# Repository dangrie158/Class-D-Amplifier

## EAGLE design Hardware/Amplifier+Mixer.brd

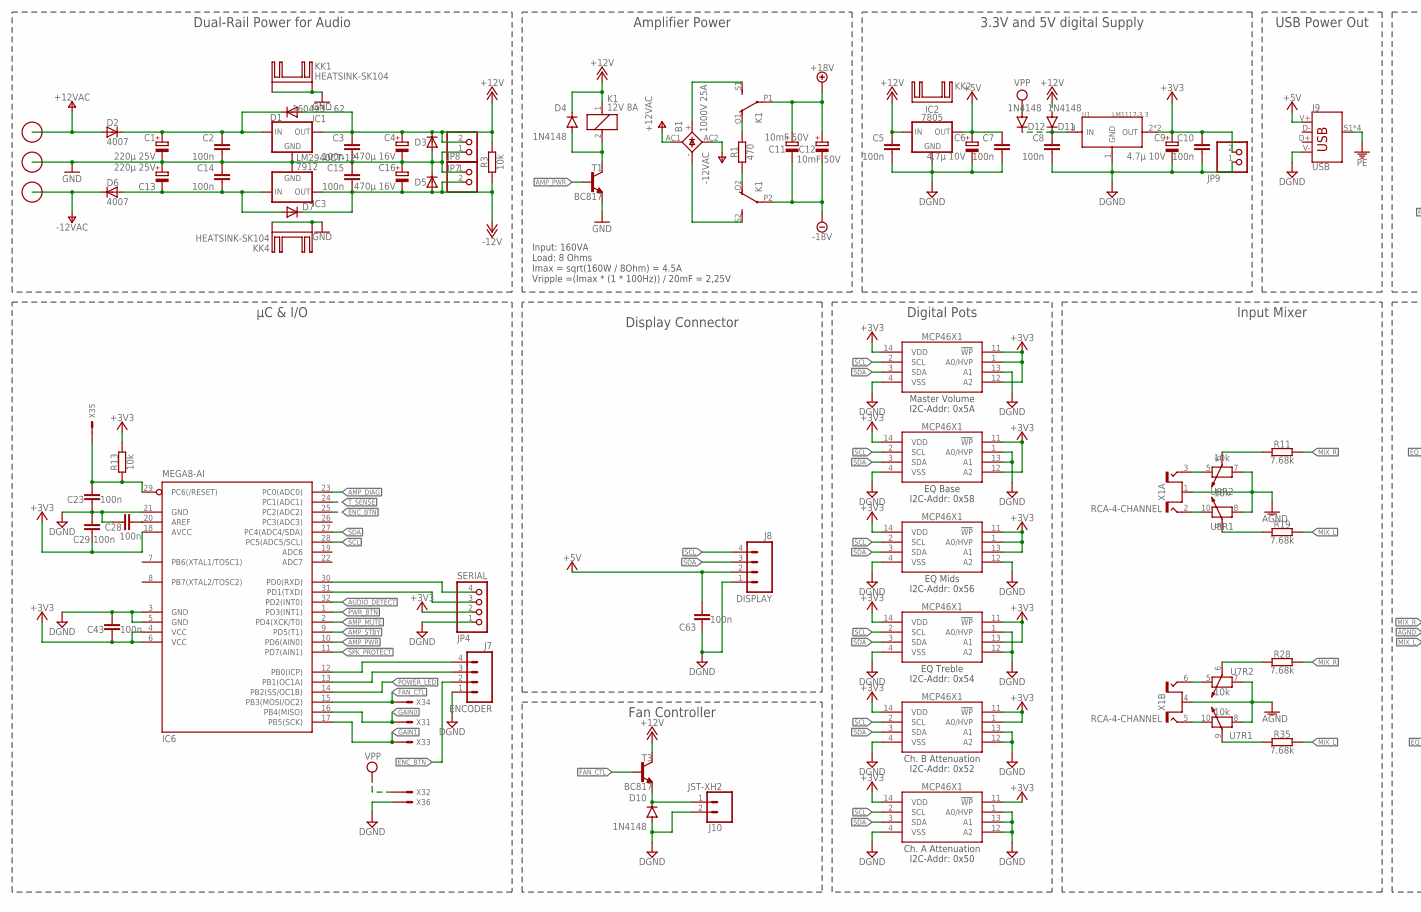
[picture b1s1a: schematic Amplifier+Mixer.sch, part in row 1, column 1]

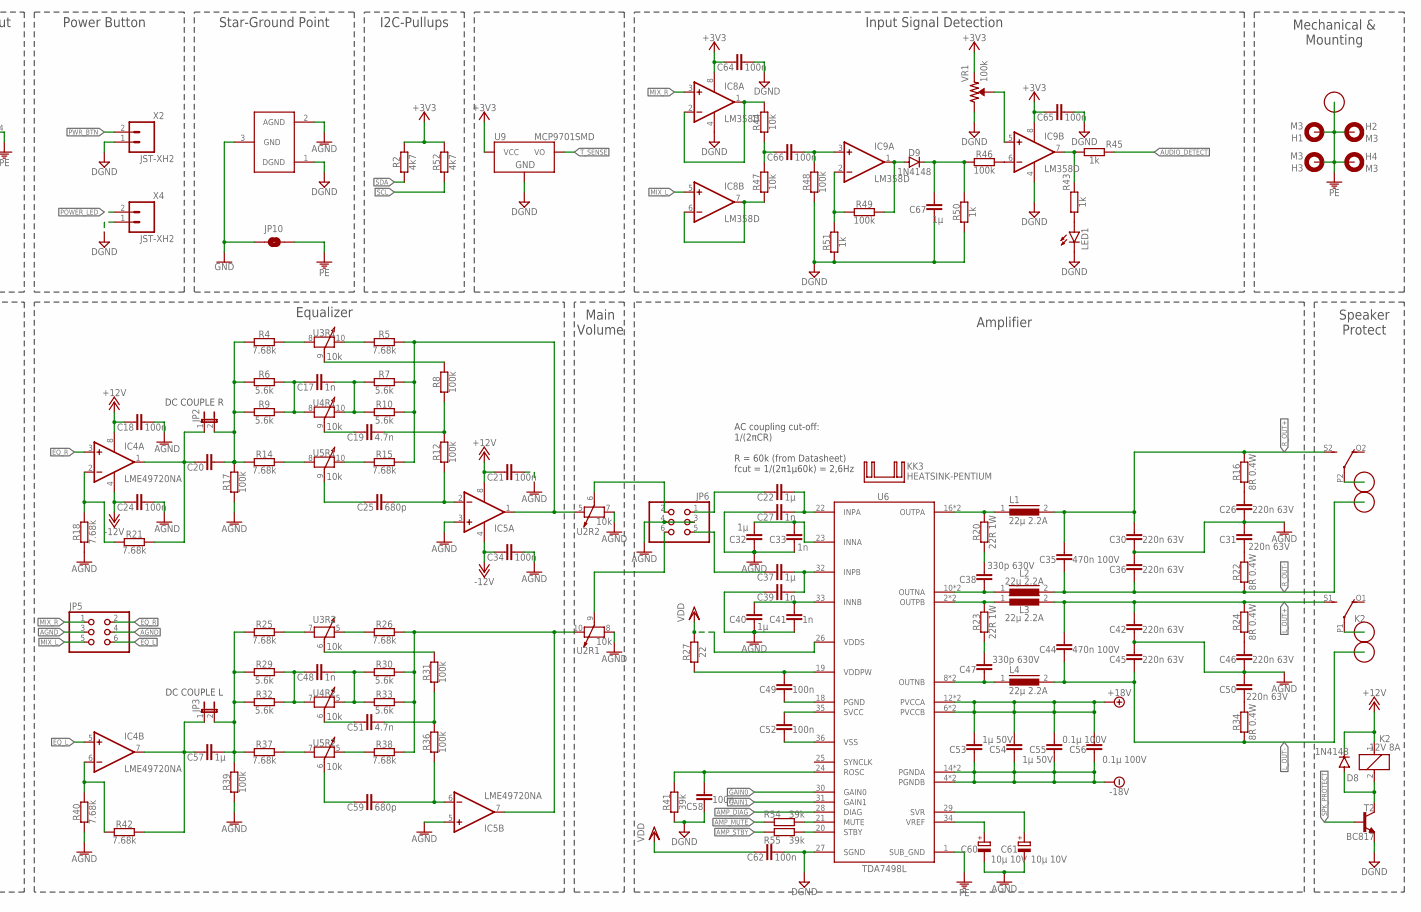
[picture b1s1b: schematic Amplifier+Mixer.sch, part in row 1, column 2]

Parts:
B1: 1000V 25A; FB100; MOUSER 833-GBJL2510-BP
C1, C13: 220µ 25V; 175TMP-0810; MOUSER 647-UWT1E221MNL1GS
C2, C3, C5, C7, C8, C10, C14, C15, C18, C21, C23, C24, C28, C29, C34, C43, C49, C52, C58, C62, C63, C64, C65, C66: 100n; C0603; MOUSER 710-885012206071
C4, C16: 470µ 16V; 175TMP-0810; MOUSER 647-UWT1C471MNL1S
C6, C9: 4.7µ 10V; 153CLV-0505; MOUSER 710-865230642008
C11, C12: 10mF 50V; EB35D; MOUSER 647-LLS1H103MELC
C17, C27, C33, C39, C41, C48: 1n; C050-025X075; MOUSER 80-R82EC1100AA50K
C19, C51: 4.7n; C075-032X103; MOUSER 594-222237188472
C20: DC COUPLE L; C050-050X075; MOUSER 80-R82DC4100AA60K
C22, C32, C37, C40, C57: 1µ; C050-050X075; MOUSER 80-R82DC4100AA60K
C25, C59: 680p; C050-045X075; MOUSER 505-FKP2J006801D00KS
C26, C30, C31, C36, C42, C45, C46, C50: 220n 63V; C050-025X075; MOUSER 80-R82DC3220AA60K
C35, C44: 470n 100V; C050-045X075; MOUSER 505-MKS2D034701E00JI
C38, C47: 330p 630V; C050-045X075; MOUSER 505-FKP2C003301D00KI
C53, C54: 1µ 50V; C1206K; MOUSER 80-C1206C105M5RECLR
C55, C56: 0.1µ 100V; C1206K; MOUSER 77-VJ1206Y104KXBAT
C60, C61: 10µ 10V; 153CLV-0505; MOUSER 710-865080642006
C67: 1µ; C0603; MOUSER 710-885012106022
D1, D2, D3, D5, D6, D7: 4007; SODFL5024X231; MOUSER 583-FM4007W-W
D4, D8, D9, D10, D11, D12: 1N4148; SOD-323; MOUSER 512-1N4148WS
H1, H2, H3, H4: M3; 3,0-PAD
IC1: LM2940CT-12; 78XXS; MOUSER 511-L7812CV
IC2: 7805; 78XXS; MOUSER 511-L7805CV
IC3: 7912; 79XXS; MOUSER 511-L7912CV
IC4, IC5: LME49720NA; DIL08
IC6: MEGA8-AI; TQFP32-08; MOUSER 556-ATMEGA328-AU
IC8, IC9: LM358D; SO08; MOUSER 511-LM358DT
J1, J2, J3, J4: 6MM; TE-726386; MOUSER 571-726386-2
J5, J6: TERMINAL-BLOCK-2PLUG-IN; MSTBV2; MOUSER 651-1954919
J7: ENCODER; JST-4-PTH-VERT; MOUSER 538-35312-0260
J8: DISPLAY; JST-4-PTH-VERT; MOUSER 538-35312-0260
J9: USB; ECON-USBBUVA; MOUSER 523-GSB19110KEU
J10: JST-XH2; JST-2-PTH-VERT; MOUSER 575-3191010200006000
JP1: GND_CONNECT
JP2: DC COULE R; JP1; MOUSER 200-TSW10223TS
JP3: DC COUPLE L; JP1; MOUSER 200-TSW10223TS
JP4: SERIAL; 1X04; MOUSER 649-68001-204HLF
JP5: MIX OUT; 2X03
JP6: PREAMP OUT; 2X03
JP7, JP8, JP9: PINHD-1X2; 1X02
JP10: PEGND; SMT-JUMPER_2_NO_NO-SILK
K1, K2: 12V 8A; F4052; MOUSER 655-RT424012
KK1, KK4: HEATSINK-SK104; SK104-PAD; MOUSER 490-HSE-B20254-035H
KK2: HEATSINK-SK95; SK95-2M3; MOUSER 490-HSE-B2111-038
KK3: HEATSINK-PENTIUM
L1, L2, L3, L4: 22µ 2.2A; INDUCTOR-12MM; MOUSER 710-744771220
LED1: LEDCHIP-LED0603; CHIP-LED0603
R1: 470; 0617/22; MOUSER 279-EP5WS470RJ
R2, R52: 4k7; R0603; MOUSER 603-AC0603JR-134K7L
R3, R13, R44, R47: 10k; R0603; MOUSER 603-RC0603FR-0710KL
R4, R5, R11, R14, R15, R18, R19, R21, R25, R26, R28, R35, R37, R38, R40, R42: 7.68k; MINI_MELF-0207W; MOUSER 71-SMM02070C7501FBP0
R6, R7, R9, R10, R29, R30, R32, R33: 5.6k; MINI_MELF-0207W; MOUSER 71-SMM02070C5601FBP0
R8, R12, R17, R31, R36, R39: 100k; MINI_MELF-0204W; MOUSER 756-WRM024HPC100KFT3
R16, R22, R24, R34: 8R 0.4W; MINI_MELF-0204W; MOUSER 756-WRM0204HPC8R2FT3
R20, R23: 22R 1W; MINI_MELF-0207W; MOUSER 756-WRM0207HPC22RFT2
R27: 22; R0603; MOUSER 603-RC0603FR-0722RL
R41: 39k; R0603; MOUSER 603-RC0603FR-0739KL
R43, R45, R50, R51: 1k; R0603; MOUSER 603-RC0603FR-071KL
R46, R48, R49: 100k; R0603; MOUSER 71-RCA0603100KJNEC
R54, R55: 39k; R0603; MOUSER 71-RCA0603100KJNEC
T1, T2, T3: BC817; SOT23-BEC; MOUSER 863-BC817-16LT3G
U1: LM1117-3.3; SOT-223; MOUSER 926-LM1117MPX3.3NOPB
U2, U3, U4, U5, U7, U8: 10k; SOP65P640X120-14; MOUSER 579-MCP4641-103E/ST
U6: TDA7498L; SOP50P1010X245-36; MOUSER 511-TDA7498TR
U9: MCP9701SMD; SOT23-3
VR1: 100k; TRIMPOT-SMD-TC33X; MOUSER 858-35WR100KLFTR
X1: RCA-4-CHANNEL; BKL-072385; MOUSER 806-KLP42X-61-WWRR
X2, X4: JST-XH2; JST-2-PTH-VERT; MOUSER 575-3191010200006000
X3: ICSP; 057-006-1; MOUSER 200-TSW10307TD

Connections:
+3V3: C9.+, C10.1, C29.1, C43.1, C64.1, C65.1, IC6.4 (VCC), IC6.6 (VCC), IC6.18 (AVCC), IC8.8 (V+), IC9.8 (V+), JP4.2, JP9.2, R2.2, R13.2, R52.2, U1.2 (OUT), U1.TER (OUT), U2.1 (A0/HVP), U2.11 (!WP), U2.12 (A2), U2.14 (VDD), U3.11 (!WP), U3.12 (A2), U3.14 (VDD), U4.1 (A0/HVP), U4.11 (!WP), U4.13 (A1), U4.14 (VDD), U5.11 (!WP), U5.13 (A1), U5.14 (VDD), U7.1 (A0/HVP), U7.11 (!WP), U7.14 (VDD), U8.11 (!WP), U8.14 (VDD), U9.1 (VCC), VR1.3 (CCW)
+5V: C6.+, C7.1, C63.2, IC2.OUT, J8.2, J9.V+ (VBUS)
+12V: C3.1, C4.+, C5.1, C18.1, C21.1, D1.A, D3.C, D4.C, D8.C, D11.A, IC1.OUT, IC2.IN, IC4.8 (V+), IC5.8 (V+), JP7.2, K1.1, K2.1, R3.1, T3.C
+18V: C11.+, C12.+, C53.1, C54.1, C55.1, C56.1, K1.P1, U6.6 (PVCCB), U6.7 (PVCCB), U6.12 (PVCCA), U6.13 (PVCCA)
-12V: C15.2, C16.-, C24.1, C34.1, D5.A, D7.C, IC3.OUT, IC4.4 (V-), IC5.4 (V-), JP8.2, R3.2
-18V: C11.-, C12.-, C53.2, C54.2, C55.2, C56.2, K1.P2, U6.4 (PGNDB), U6.5 (PGNDB), U6.14 (PGNDA), U6.15 (PGNDA)
AGND: C18.2, C21.2, C24.2, C26.2, C27.1, C30.2, C31.1, C32.1, C33.1, C34.2, C36.1, C39.1, C40.1, C41.1, C42.2, C45.1, C46.2, C50.1, C60.-, C61.-, IC5.3 (+IN), IC5.5 (+IN), JP1.2 (AGND), JP5.3, JP5.4, JP6.3, JP6.4, R17.1, R18.2, R39.1, R40.2, U2.7 (A), U2.8 (A), U7.7 (A), U7.8 (A), U8.7 (A), U8.8 (A), X1.1 (S), X1.4 (S)
AMP_DIAG: IC6.23 (PC0(ADC0)), U6.28 (DIAG)
AMP_MUTE: IC6.2 (PD4(XCK/T0)), R54.2
AMP_MUTE_CL: R54.1, U6.21 (MUTE)
AMP_PWR: IC6.10 (PD6(AIN0)), T1.B
AMP_STBY: IC6.9 (PD5(T1)), R55.2
AMP_STBY_CL: R55.1, U6.20 (STBY)
AUDIO_DETECT: IC6.32 (PD2(INT0)), R45.1
DGND: C5.2, C6.-, C7.2, C8.2, C9.-, C10.2, C23.1, C28.2, C29.2, C43.2, C58.2, C62.1, C63.1, C64.2, C65.2, C67.1, D10.A, IC2.GND, IC6.3 (GND), IC6.5 (GND), IC6.21 (GND), IC8.4 (V-), IC9.4 (V-), J7.1, J8.1, J9.V- (GND), J10.2, JP1.1 (DGND), JP4.1, JP9.1, LED1.C, R41.1, R48.1, R50.1, R51.1, T2.E, U1.1 (GND), U2.4 (VSS), U2.13 (A1), U3.1 (A0/HVP), U3.4 (VSS), U3.13 (A1), U4.4 (VSS), U4.12 (A2), U5.1 (A0/HVP), U5.4 (VSS), U5.12 (A2), U6.27 (SGND), U7.4 (VSS), U7.12 (A2), U7.13 (A1), U8.1 (A0/HVP), U8.4 (VSS), U8.12 (A2), U8.13 (A1), U9.3 (GND), VR1.1 (CW), X2.1, X3.6, X4.1
ENC_BTN: IC6.25 (PC2(ADC2)), J7.2
EQ_L: IC4.5 (+IN), JP5.6
EQ_OUT_L: IC5.7 (OUT), R26.1, R30.1, R33.1, R38.1, U2.10 (B)
EQ_OUT_R: IC5.1 (OUT), R5.1, R7.1, R10.1, R15.1, U2.5 (B)
EQ_R: IC4.3 (+IN), JP5.2
FAN_CTL: IC6.15 (PB3(MOSI/OC2)), T3.B, X3.4
GAIN0: IC6.16 (PB4(MISO)), U6.30 (GAIN0), X3.1
GAIN1: IC6.17 (PB5(SCK)), U6.31 (GAIN1), X3.3
GND: C1.-, C2.2, C3.2, C4.-, C13.+, C14.1, C15.1, C16.+, D3.A, D5.C, IC1.GND, IC3.GND, J2.P$1, J2.P$2, JP1.3 (GND), JP7.1, JP8.1, JP10.1, KK1.K1, KK1.K2, KK4.K1, KK4.K2, T1.E
INNA: C32.2, C33.2, U6.23 (INNA)
INNB: C40.2, C41.2, U6.33 (INNB)
INPA: C22.2, C27.2, U6.22 (INPA)
INPB: C37.2, C39.2, U6.32 (INPB)
L_OUT+: C42.1, C44.1, K2.S1 (S), L3.2, R24.2
L_OUT-: C44.2, C45.2, J6.1, L4.2, R34.1
MIX_AMP_L: C57.1, IC4.7 (OUT), JP3.1, R42.1
MIX_AMP_R: C20.1, IC4.1 (OUT), JP2.1, R21.1
MIX_L: IC8.5 (+IN), JP5.5, R19.2, R35.2
MIX_R: IC8.3 (+IN), JP5.1, R11.2, R28.2
unnamed: C20.2, JP2.2, R4.2, R6.2, R9.2, R14.2, R17.2
unnamed: R14.1, U5.8 (A)
unnamed: C25.2, U5.9 (W)
unnamed: R15.2, U5.10 (B)
unnamed: C17.1, R6.1, R9.1, U4.8 (A)
unnamed: C57.2, JP3.2, R25.2, R29.2, R32.2, R37.2, R39.2
unnamed: R8.2, U3.9 (W)
unnamed: R31.2, U3.6 (W)
unnamed: B1.+, K1.S1 (S)
unnamed: R26.2, U3.5 (B)
unnamed: C19.2, U4.9 (W)
unnamed: C19.1, R8.1, R12.2
unnamed: C66.1, R44.1, R47.2
unnamed: R25.1, U3.7 (A)
unnamed: C17.2, R7.2, R10.2, U4.10 (B)
unnamed: C59.2, U5.6 (W)
unnamed: C51.2, U4.6 (W)
unnamed: R4.1, U3.8 (A)
unnamed: C48.1, R29.1, R32.1, U4.7 (A)
unnamed: C48.2, R30.2, R33.2, U4.5 (B)
unnamed: R37.1, U5.7 (A)
unnamed: R38.2, U5.5 (B)
unnamed: C13.-, C14.2, D6.A, D7.A, IC3.IN
unnamed: C1.+, C2.1, D1.C, D2.C, IC1.IN
unnamed: C66.2, IC9.3 (+IN), R48.2
unnamed: C52.2, U6.36 (VSS)
unnamed: B1.-, K1.S2 (S)
unnamed: R5.2, U3.10 (B)
unnamed: C51.1, R31.1, R36.2
unnamed: C52.1, U6.35 (SVCC)
unnamed: IC9.2 (-IN), R49.2, R51.2
unnamed: D9.A, IC9.1 (OUT), R49.1
unnamed: C67.2, D9.C, R46.2, R50.2
unnamed: IC9.6 (-IN), R46.1
unnamed: IC9.5 (+IN), VR1.2 (WIPER)
unnamed: IC9.7 (OUT), R43.1, R45.2
unnamed: LED1.A, R43.2
unnamed: IC8.6 (-IN), IC8.7 (OUT), R47.1
unnamed: IC8.1 (OUT), IC8.2 (-IN), R44.2
unnamed: U7.5 (B), X1.6 (T2)
unnamed: U7.10 (B), X1.5 (T1)
unnamed: R35.1, U7.9 (W)
unnamed: R28.1, U7.6 (W)
unnamed: IC4.6 (-IN), R40.1, R42.2
unnamed: IC4.2 (-IN), R18.1, R21.2
unnamed: U8.5 (B), X1.3 (T2)
unnamed: U8.10 (B), X1.2 (T1)
unnamed: R19.1, U8.9 (W)
unnamed: R11.1, U8.6 (W)
unnamed: D4.A, K1.2, T1.C
unnamed: J6.2, K2.P1
unnamed: K1.O1 (O), R1.1
unnamed: C58.1, R41.2, U6.24 (ROSC)
unnamed: C49.1, R27.1, U6.19 (VDDPW)
unnamed: C49.2, U6.18 (PGND)
unnamed: C8.1, D11.C, D12.C, U1.3 (IN)
unnamed: K1.O2 (O), R1.2
unnamed: J5.1, K2.P2
unnamed: C50.2, R34.2
unnamed: D10.C, J10.1, T3.E
unnamed: C46.1, R24.1
unnamed: C60.+, U6.34 (VREF)
unnamed: C61.+, U6.29 (SVR)
unnamed: C31.2, R22.2
unnamed: C26.1, R16.1
unnamed: C47.2, L4.1, U6.8 (OUTNB), U6.9 (OUTNB)
unnamed: C38.2, L2.1, U6.10 (OUTNA), U6.11 (OUTNA)
unnamed: C38.1, R20.1
unnamed: C47.1, R23.1
unnamed: L1.1, R20.2, U6.16 (OUTPA), U6.17 (OUTPA)
unnamed: L3.1, R23.2, U6.2 (OUTPB), U6.3 (OUTPB)
unnamed: D8.A, K2.2, T2.C
unnamed: IC6.13 (PB1(OC1A)), J7.3
unnamed: C28.1, IC6.20 (AREF)
unnamed: IC6.12 (PB0(ICP)), J7.4
unnamed: C22.1, JP6.1
unnamed: C23.2, IC6.29 (PC6(/RESET)), R13.1, X3.5
unnamed: C37.1, JP6.5
unnamed: IC6.30 (PD0(RXD)), JP4.4
unnamed: IC6.31 (PD1(TXD)), JP4.3
OUT_L_DAMPED: C59.1, IC5.6 (-IN), R36.1
OUT_R_DAMPED: C25.1, IC5.2 (-IN), R12.1
PE: H1.B3,0, H2.B3,0, H3.B3,0, H4.B3,0, J4.P$1, J4.P$2, J9.S1 (SHIELD), J9.S2 (SHIELD), J9.S3 (SHIELD), J9.S4 (SHIELD), JP10.2, U6.1 (SUB_GND)
POWER_LED: IC6.14 (PB2(SS/OC1B)), X4.2
PREAMP_OUT_L: JP6.6, U2.9 (W)
PREAMP_OUT_R: JP6.2, U2.6 (W)
PWR_BTN: IC6.1 (PD3(INT1)), X2.2
R_OUT+: C30.1, C35.1, K2.S2 (S), L1.2, R16.2
R_OUT-: C35.2, C36.2, J5.2, L2.2, R22.1
SCL: IC6.28 (PC5(ADC5/SCL)), J8.4, R52.1, U2.2 (SCL), U3.2 (SCL), U4.2 (SCL), U5.2 (SCL), U7.2 (SCL), U8.2 (SCL)
SDA: IC6.27 (PC4(ADC4/SDA)), J8.3, R2.1, U2.3 (SDA), U3.3 (SDA), U4.3 (SDA), U5.3 (SDA), U7.3 (SDA), U8.3 (SDA)
SPK_PROTECT: IC6.11 (PD7(AIN1)), T2.B
T_SENSE: IC6.24 (PC1(ADC1)), U9.2 (VO)
V+: B1.AC1, D2.A, J1.P$1, J1.P$2
V-: B1.AC2, D6.C, J3.P$1, J3.P$2
VDD: C62.2, R27.2, U6.26 (VDDS)
VPP: D12.A, X3.2

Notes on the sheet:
I2C-Addr: 0x50
I2C-Addr: 0x52
I2C-Addr: 0x54
I2C-Addr: 0x56
I2C-Addr: 0x58
I2C-Addr: 0x5A
Ch. A Attenuation
Ch. B Attenuation
EQ Treble
EQ Mids
EQ Base
Master Volume
Amplifier
Speaker Protect
Main Volume
Equalizer
Input Mixer
Digital Pots
Display Connector
Fan Controller
µC & I/O
Input Signal Detection
Amplifier Power
Dual-Rail Power for Audio
3.3V and 5V digital Supply
USB Power Out
Power Button
Star-Ground Point
Mechanical & Mounting
I2C-Pullups
DC COUPLE L
DC COUPLE R
Input: 160VA Load: 8 Ohms Imax = sqrt(160W / 8Ohm) = 4.5A Vripple =(Imax * (1 * 100Hz)) / 20mF = 2,25V
AC coupling cut-off: 1/(2πCR) R = 60k (from Datasheet) fcut = 1/(2π1µ60k) = 2,6Hz

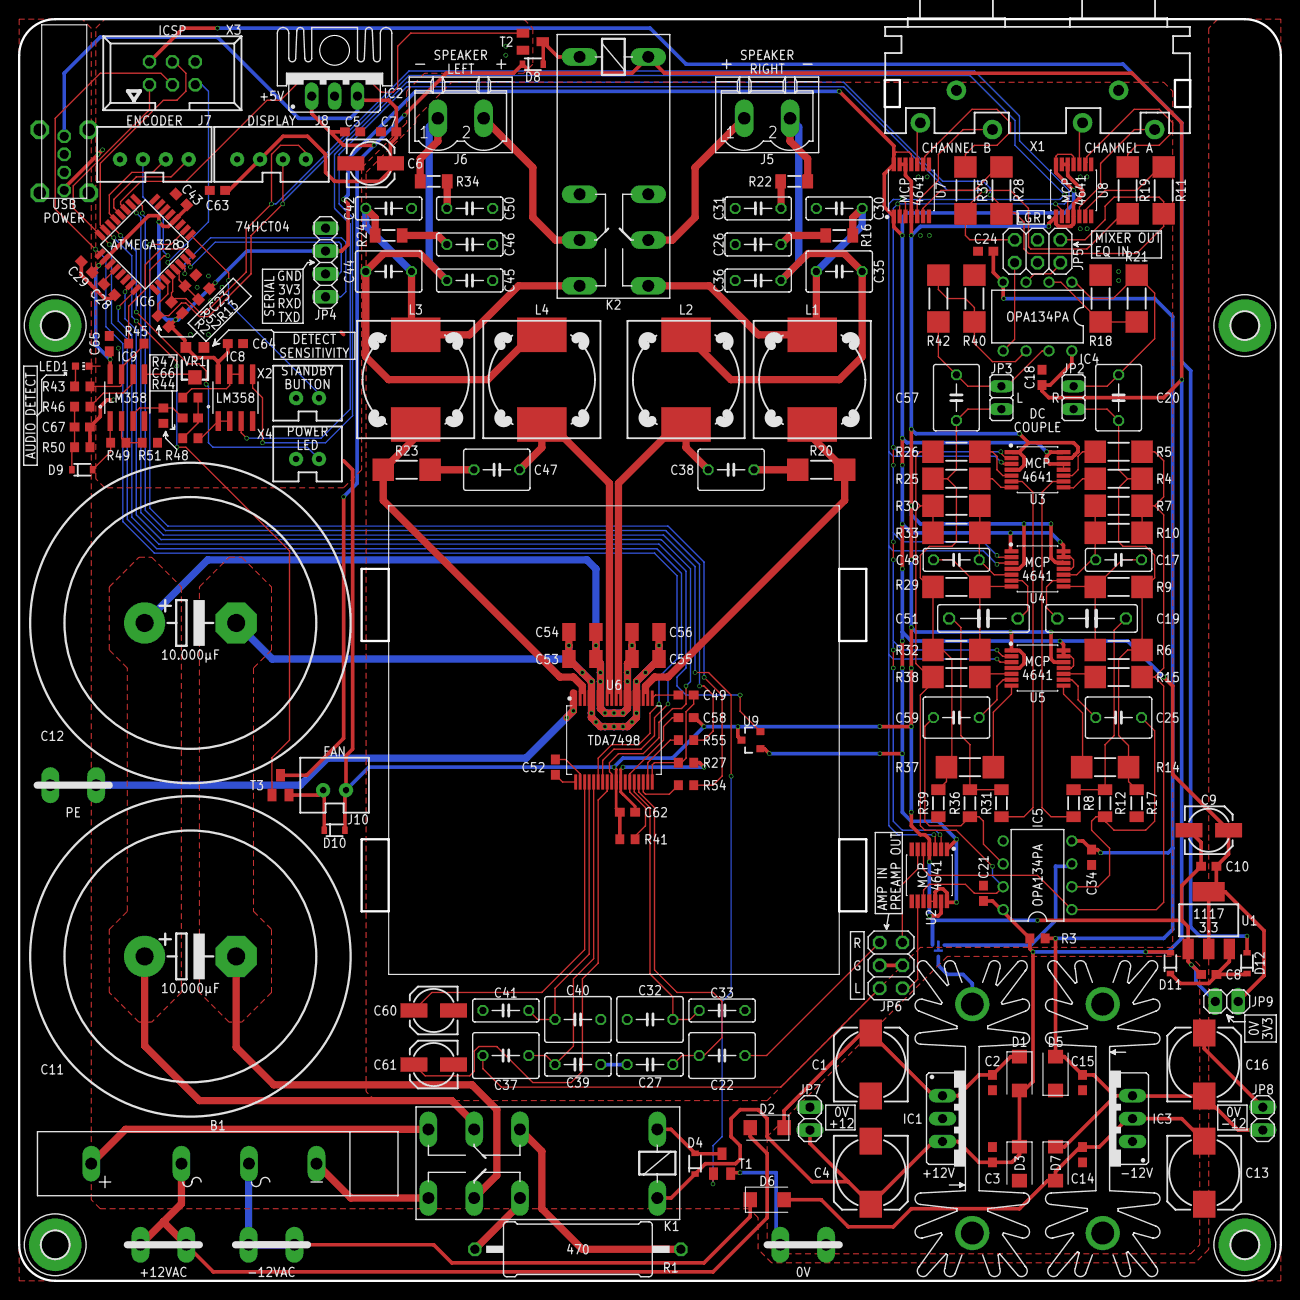
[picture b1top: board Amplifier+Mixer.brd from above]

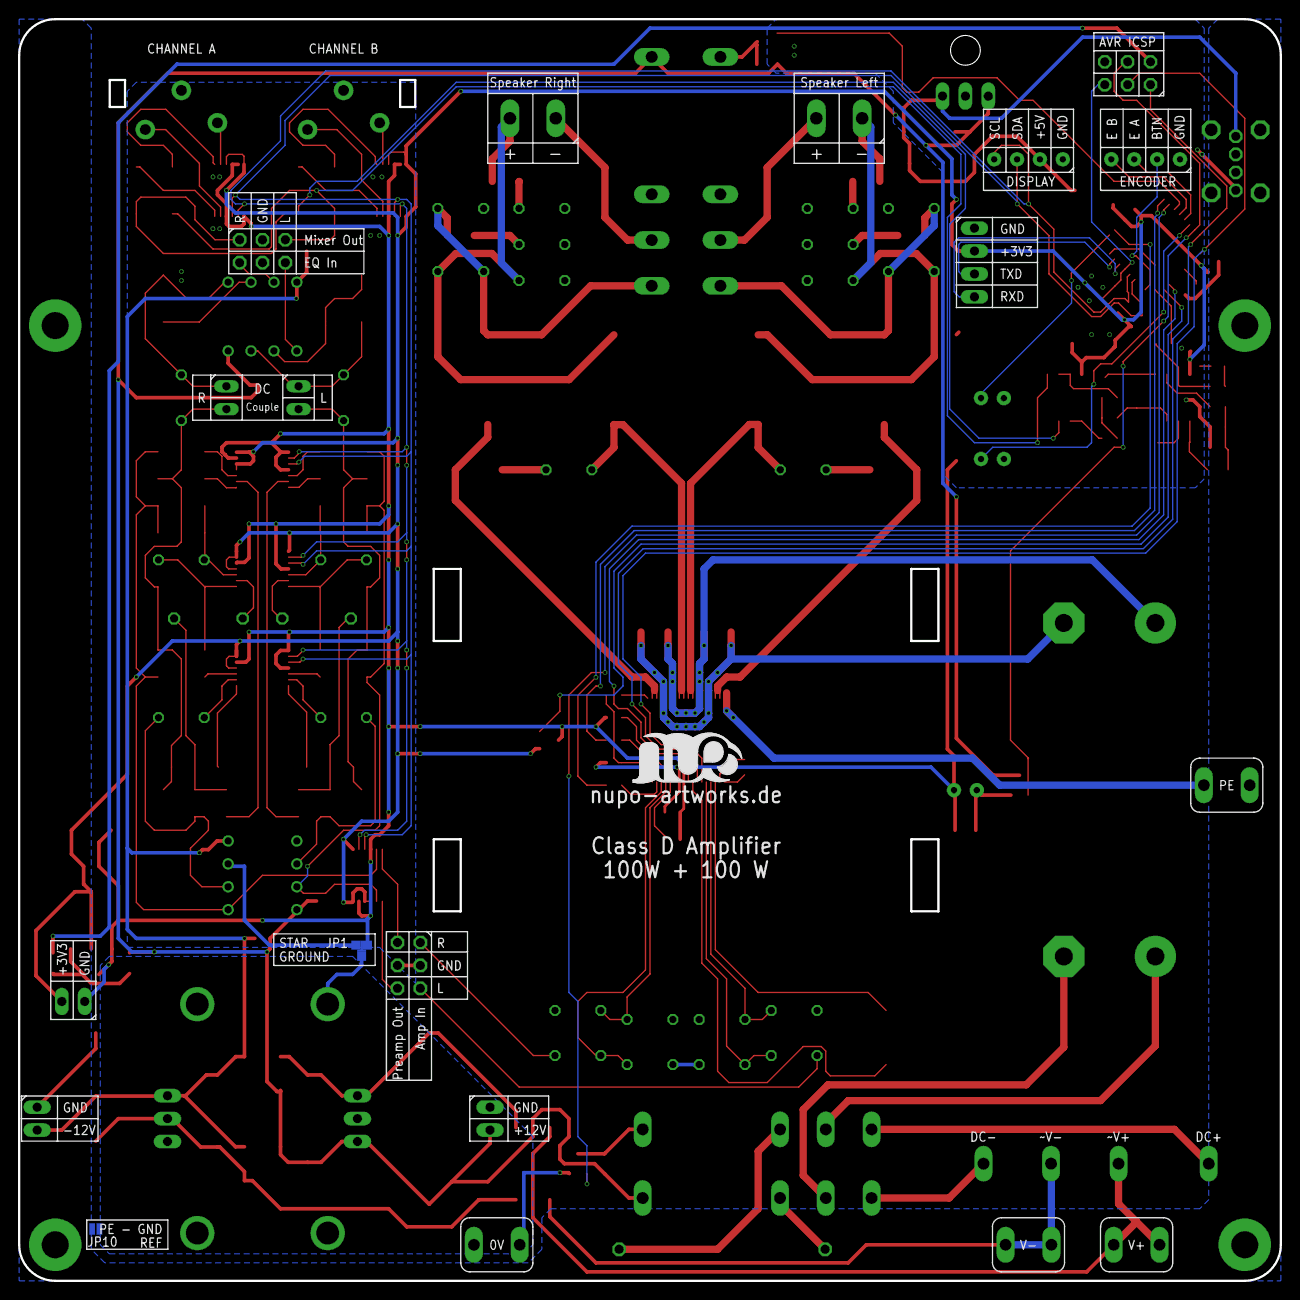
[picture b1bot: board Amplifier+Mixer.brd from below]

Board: 2 copper layers, 140.0 x 140.0 mm, 195 parts (3 on the bottom side), 131 nets.

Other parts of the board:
U$1: LOGO-SILKSCREEN

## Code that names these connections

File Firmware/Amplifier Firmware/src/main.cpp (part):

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
#include "Settings.h"
// pin definitions & mapping
#define AUDIO_DETECT 2
#define POWER_BTN 3
#define AMP_MUTE 4
#define AMP_STANDBY 5
#define AMP_POWER 6
#define SPEAKER_PROTECT 7
#define ENC_A 8
#define ENC_B 9
#define POWER_LED 10
#define FAN_CTRL 11
#define PIN_GAIN0 12
#define PIN_GAIN1 13
#define AMP_DIAG A0
#define T_SENSE A1
#define ENC_BTN A2

// MCP46X1 register addresses
// bits 4-8 in the command byte
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  switch (setting->value)
  {
  case 0: // 25.6dB
    digitalWrite(PIN_GAIN0, LOW);
    digitalWrite(PIN_GAIN1, LOW);
    break;
  case 1: // 31.6dB
    digitalWrite(PIN_GAIN0, LOW);
    digitalWrite(PIN_GAIN1, HIGH);
    break;
  case 2: // 35.6dB
    digitalWrite(PIN_GAIN0, HIGH);
    digitalWrite(PIN_GAIN1, LOW);
    break;
  case 3: // 37.6dB
    digitalWrite(PIN_GAIN0, HIGH);
    digitalWrite(PIN_GAIN1, HIGH);
    break;
  }
}
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
  
  // setup GPIO data direction for all pins
  pinMode(AUDIO_DETECT, INPUT);
  pinMode(POWER_BTN, INPUT_PULLUP);
  pinMode(AMP_MUTE, OUTPUT);
  pinMode(AMP_STANDBY, OUTPUT);
  pinMode(AMP_POWER, OUTPUT);
  pinMode(SPEAKER_PROTECT, OUTPUT);
  pinMode(ENC_A, INPUT_PULLUP);
  pinMode(ENC_B, INPUT_PULLUP);
  pinMode(ENC_BTN, INPUT_PULLUP);
  pinMode(FAN_CTRL, OUTPUT);
  pinMode(PIN_GAIN0, OUTPUT);
  pinMode(PIN_GAIN1, OUTPUT);
  pinMode(AMP_DIAG, INPUT_PULLUP);
  pinMode(T_SENSE, INPUT);
  pinMode(POWER_LED, OUTPUT);

  //Start the timer 1 to service the click encoder every 1ms
  Timer1.initialize(1000);
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
  // setup the power button and audio detect interrupt
  attachInterrupt(digitalPinToInterrupt(POWER_BTN), powerButtonISR, FALLING);
  attachInterrupt(digitalPinToInterrupt(AUDIO_DETECT), audioDetectISR, CHANGE);

  targetPowerState = POWER_ON;
  
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
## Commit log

2019-02-11 moved info to mechanical files
2019-02-11 Modularized schematic and cleaned up component designators
2019-02-11 consolidated some components to minimize BOM
2019-02-13 added BOM and tooling to backannotate BOM to attributes
2019-02-13 added order numbers for conrad and mouser as attributes of the parts
2019-02-17 first routing pass
2019-02-18 first silkscreen placement pass
2019-02-18 added temp sensor for amp chip heatsink
2019-02-18 improved temp sensor routing
2019-02-18 added power led connector
2019-02-20 removed 74hct04 for level shifting
2019-02-21 removed gain selection dip switch and wired gain pins to µC
2019-02-21 added first firmware functions
2019-02-22 added indicator LED to audio detection circuit
2019-02-22 moved power led to pwm capable pin
2019-02-23 implemented firmware state diagram
2019-02-23 added flowchart for firmare logic
2019-02-23 added fan speed control dependent on heatsink temperature
2019-03-17 fixed i2c communication with epots
2019-03-17 fixed feedback network in mixer buffer output stage
2019-10-22 updated to newest version
2019-10-22 added static version of component library

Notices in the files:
parts and their libraries:
SparkFun-DiscreteSemi: Licensing: Creative Commons ShareAlike 4.0 International - https://creativecommons.org/licenses/by-sa/4.0
